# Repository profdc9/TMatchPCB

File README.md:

# T Match Antenna Tuner on a PCB

This is a QRP antenna tuner with the capacitor and inductor implemented on a PCB.  The capacitor is a split-stator capacitor that is tuned by sliding a second PCB over the tuner PCB to change the contact area.  The inductor is a spiral inductor with eight taps with switches for selecting the tap.  There is a resistive bridge built into the tuner to aid in tuning the antenna.  Ruled lines are drawn on the silkscreen so that the capacitor positions can be noted.

The moving plate is bolted through a hole to and a slot to the antenna tuner plate, with the copper sides (sides without the rulings) face-to-face.  Washers should be used on both sides of the plates to spread out the clamping force, with a screw or bolt head on the bottom side, and a wing nut on the top side, to make the two plates easy to loosen, slide, and retighten in a new position.

The rough guide to tuning a T-match.
- Switch the tuner bridge from BYP to MEAS.  Set the transmitter for low power (less than 5 W) in case the transmitter is capable than more than this power.
- Set the capacitor plates on the antenna side for maximum overlap and those on the transmit side for half overlap.
- Switching only one inductor switch at a time, find the position which dims the LED the most.
- Slide and retighten the capacitor on the transmitter side to dim the LED.
- Test the other inductor settings to see if the LED can be further dimmed (antenna better matched).  Alternate between the transmitter capacitor and inductor to minimize the LED brightness.
- After tuning the input capacitor and inductor switch, adjust the antenna side capacitor for minimum brightness.  Once you have done this, repeat returning the transmit side capacitor and inductor.  The goal is to maximize the antenna side capacitance while achieving a good match with the transmit side capacitor and inductor tap.
- Record which inductor tap is switched and the position of the plates as indicated by the ruled line position on the edge of the tuner plate for the transmit and antenna side capacitors.
- Switch the tuner bridge from MEAS to BYP before transmitting.

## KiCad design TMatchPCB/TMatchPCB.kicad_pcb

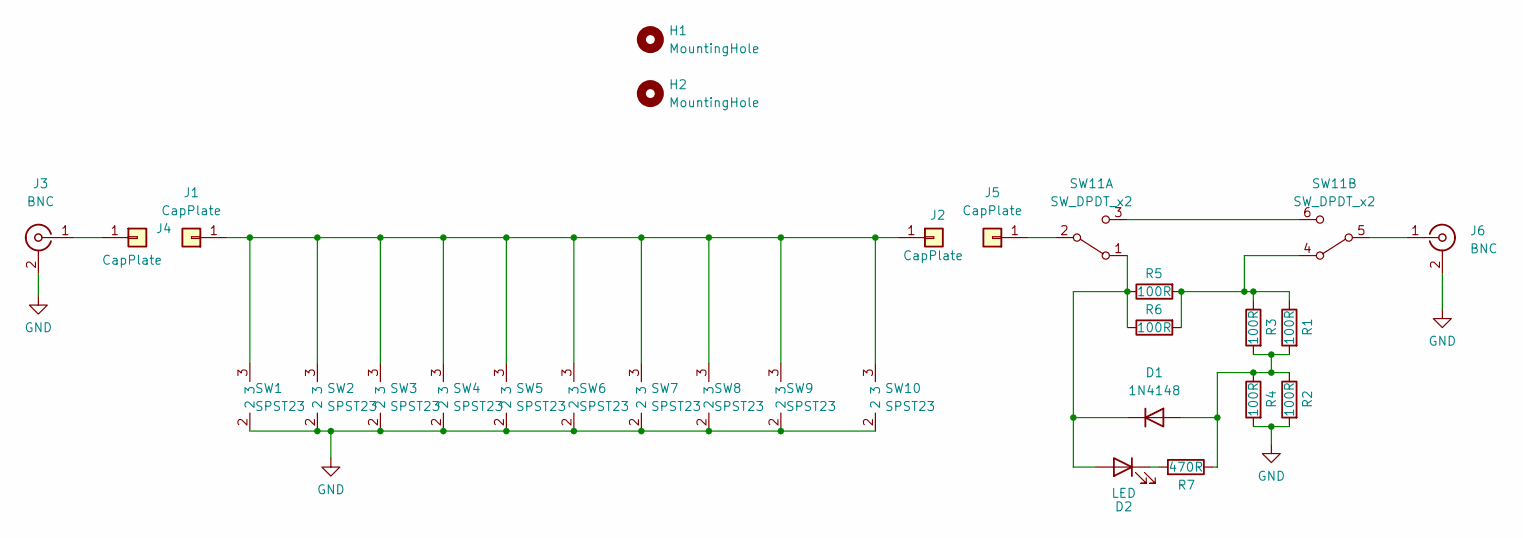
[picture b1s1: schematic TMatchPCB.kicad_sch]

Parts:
D1: 1N4148; D_DO-35_SOD27_P7.62mm_Horizontal
D2: LED; LED_D3.0mm
H1, H2: MountingHole; SlideSlot
J1, J2, J4, J5: CapPlate
J3, J6: BNC; bnc_90_1-1337543-0_pad_combo
R1, R2, R3, R4, R5, R6: 100R; R_Axial_DIN0309_L9.0mm_D3.2mm_P12.70mm_Horizontal
R7: 470R; R_Axial_DIN0207_L6.3mm_D2.5mm_P7.62mm_Horizontal
SW1, SW2, SW3, SW4, SW5, SW6, SW7, SW8, SW9, SW10: SPST23; SS22NB
SW11: SW_DPDT_x2; SS22

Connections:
GND: J3.2 (Ext), J6.2 (Ext), R2.2, R4.2, SW1.2, SW2.2, SW3.2, SW4.2, SW5.2, SW6.2, SW7.2, SW8.2, SW9.2, SW10.2
unnamed: D2.1 (K), R7.2
unnamed: D1.1 (K), D2.2 (A), R5.1, R6.1, SW11.1 (A)
unnamed: J1.1, J2.1, SW1.3, SW2.3, SW3.3, SW4.3, SW5.3, SW6.3, SW7.3, SW8.3, SW9.3, SW10.3
unnamed: J3.1 (In), J4.1
unnamed: J5.1, SW11.2 (B)
unnamed: J6.1 (In), SW11.5 (B)
unnamed: R1.1, R3.1, R5.2, R6.2, SW11.4 (A)
unnamed: D1.2 (A), R1.2, R2.1, R3.2, R4.1, R7.1
unnamed: SW11.3 (C), SW11.6 (C)

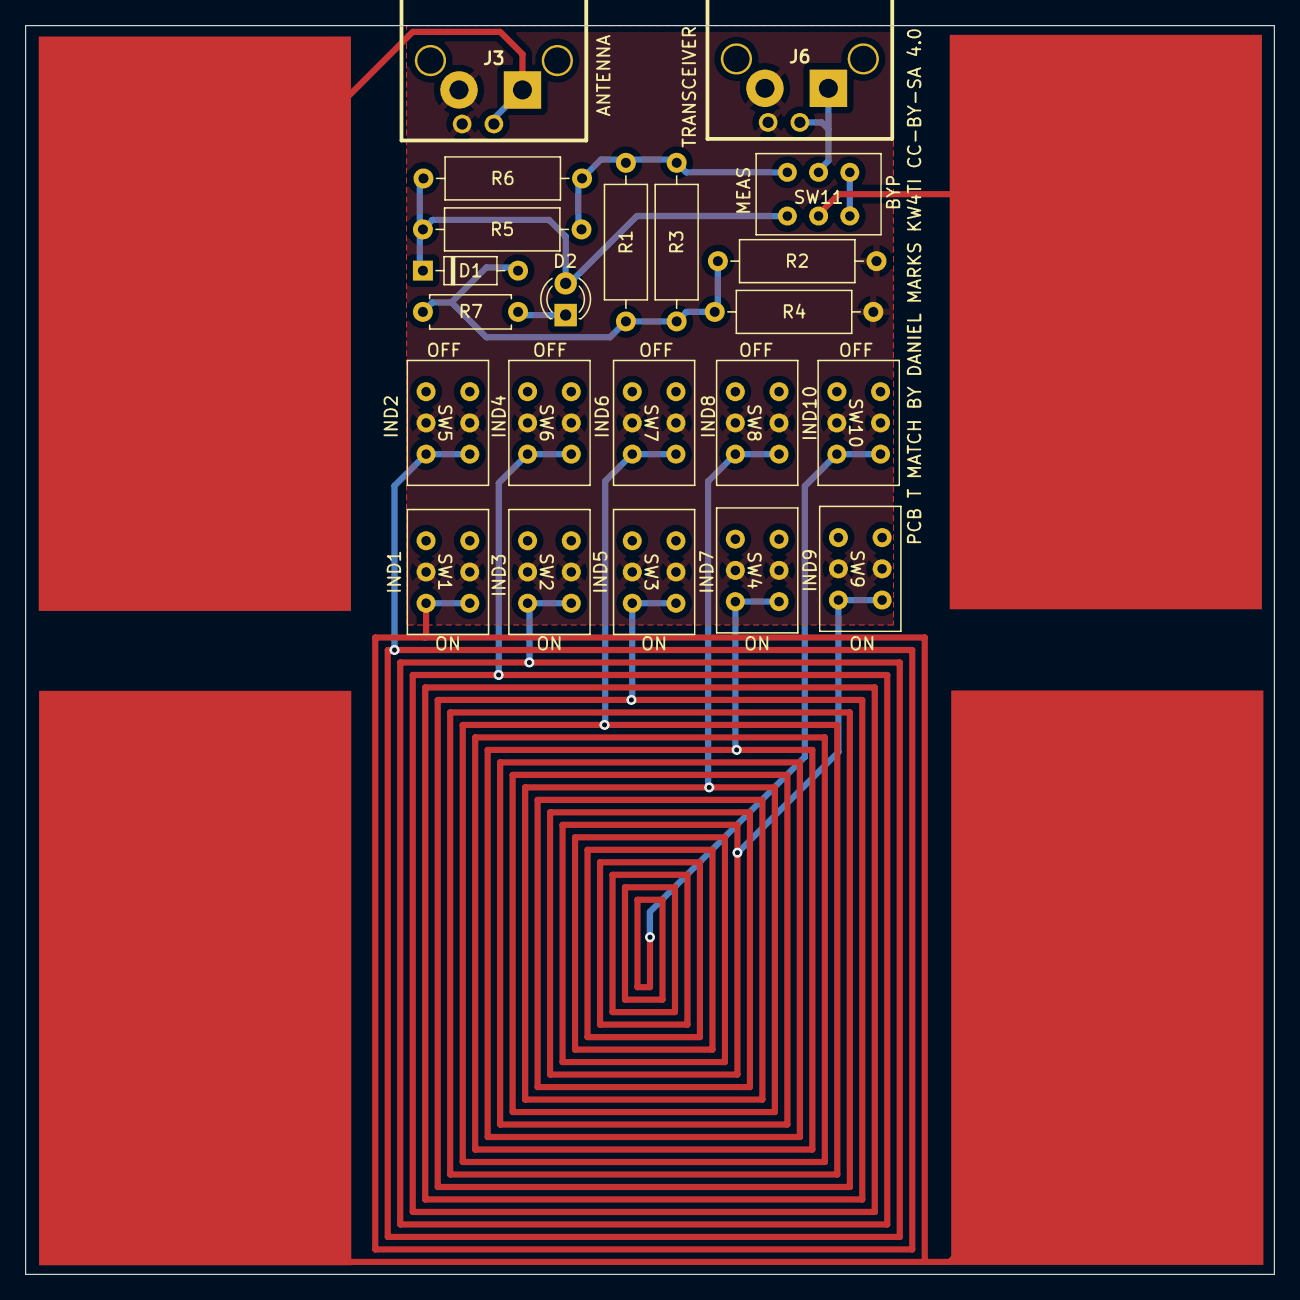
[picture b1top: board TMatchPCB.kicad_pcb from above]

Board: 2 copper layers, 100.0 x 100.0 mm, 28 parts (0 on the bottom side), 10 nets.

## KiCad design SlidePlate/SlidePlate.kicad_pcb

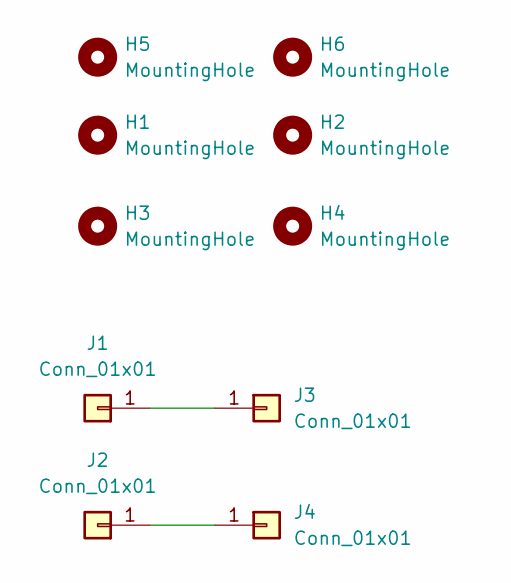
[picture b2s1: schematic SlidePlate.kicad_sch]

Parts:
H1, H2, H3, H4, H5, H6: MountingHole; MountingHole_3.7mm
J1, J2, J3, J4: Conn_01x01; CapPlate

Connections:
unnamed: J1.1, J3.1
unnamed: J2.1, J4.1

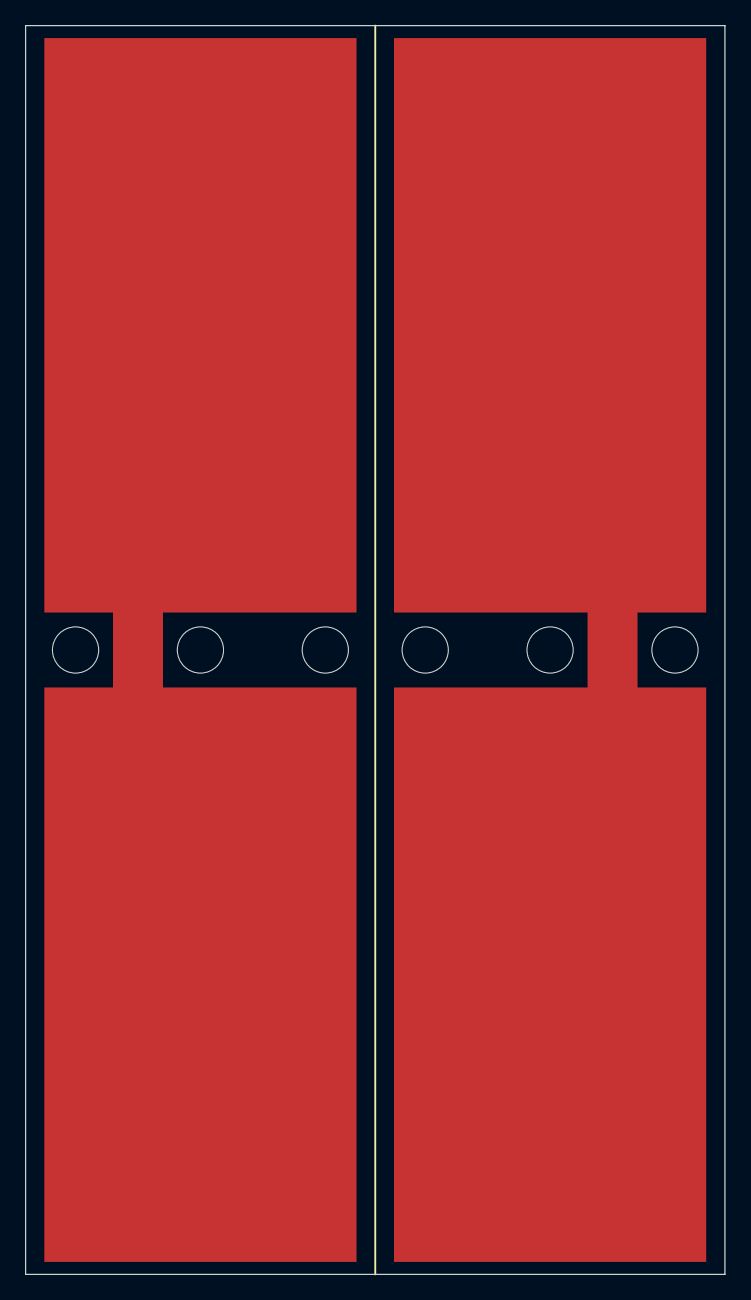
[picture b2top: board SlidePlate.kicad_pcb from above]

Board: 2 copper layers, 56.0 x 100.0 mm, 10 parts (0 on the bottom side), 2 nets.

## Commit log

2023-04-03 Added vernier lines
2023-04-03 Added more ruled lines
2023-04-04 Modified resistive bridge
2023-04-09 Added 2 more taps for inductor
2023-04-09 Tightened up board layout
2023-04-28 Picture of assembled T Match
2023-05-03 Fixed taps
2023-06-08 Added silkscreen instructions and one slide plate

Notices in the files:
SlidePlate/SlidePlate.kicad_pcb:
SLIDE PLATE BY DANIEL MARKS KW4TI CC-BY-SA 4.0
TMatchPCB/TMatchPCB.kicad_pcb:
PCB T MATCH BY DANIEL MARKS KW4TI CC-BY-SA 4.0
